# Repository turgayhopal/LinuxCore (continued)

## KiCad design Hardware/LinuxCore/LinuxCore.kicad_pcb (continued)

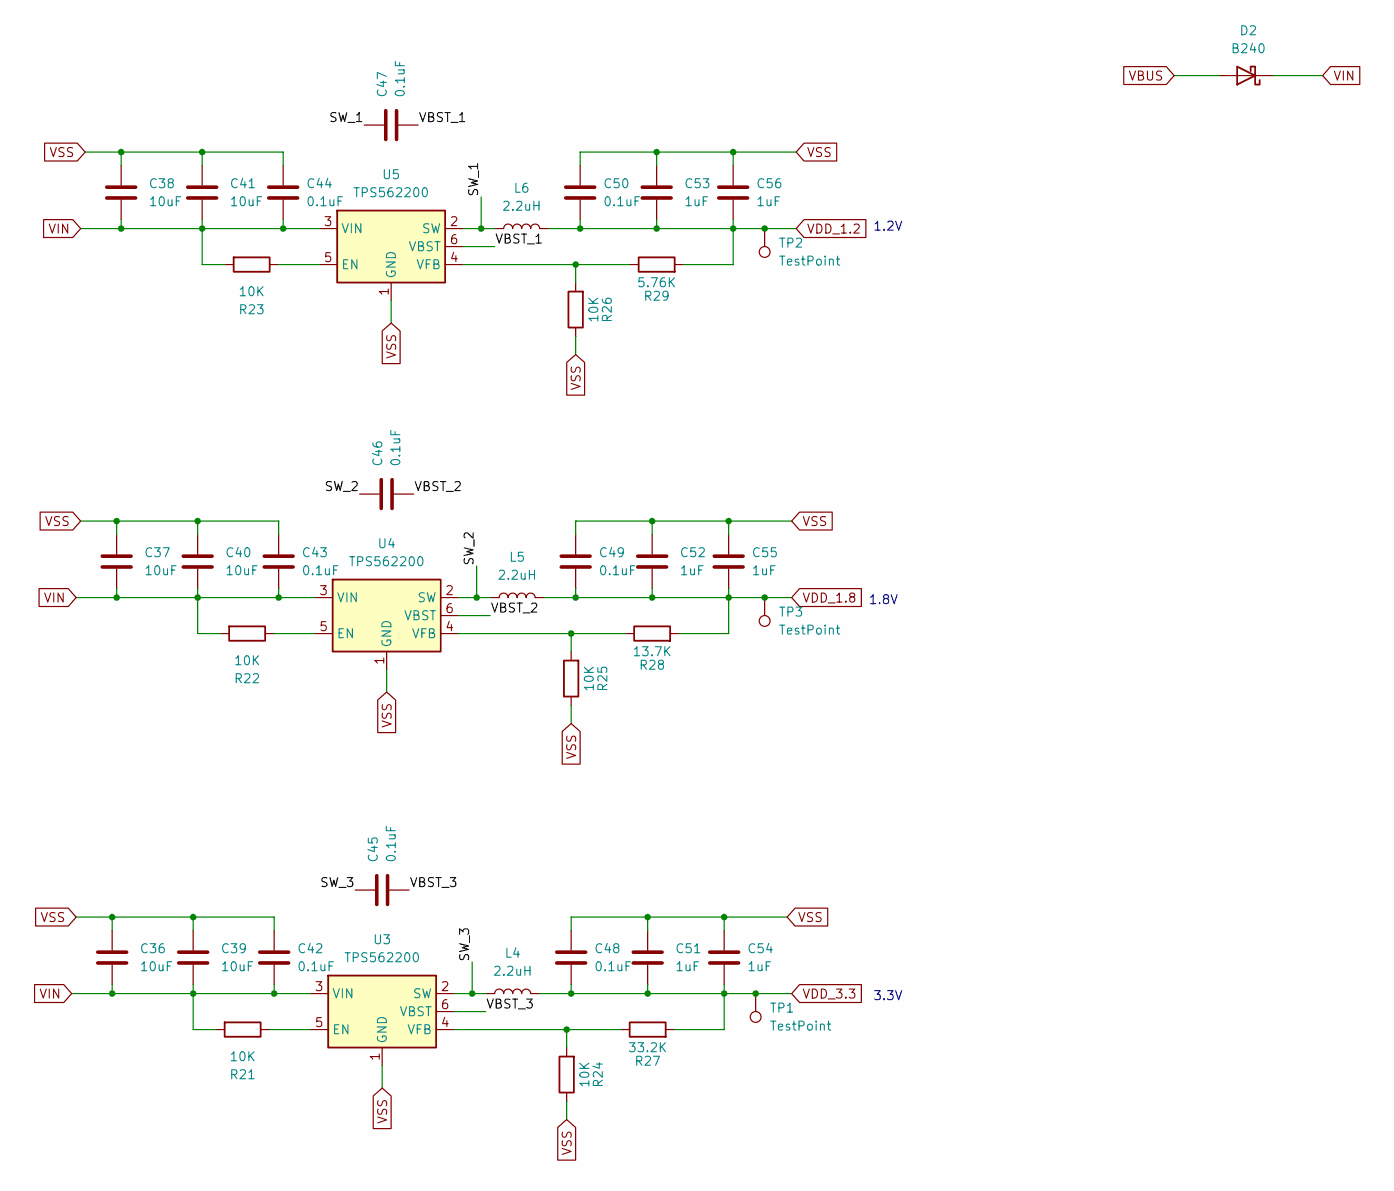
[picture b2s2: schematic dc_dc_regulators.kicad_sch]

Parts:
C36, C37, C38, C39, C40, C41: 10uF; C_0402_1005Metric
C42, C43, C44, C45, C46, C47, C48, C49, C50: 0.1uF; C_0402_1005Metric
C51, C52, C53, C54, C55, C56: 1uF; C_0402_1005Metric
D2: B240; D_SOD-123
L4, L5, L6: 2.2uH; L_Wuerth_MAPI-3020
R21, R22, R23, R24, R25, R26: 10K; R_0402_1005Metric
R27: 33.2K; R_0402_1005Metric
R28: 13.7K; R_0402_1005Metric
R29: 5.76K; R_0402_1005Metric
TP1, TP2, TP3: TestPoint; TestPoint_Pad_D1.0mm
U3, U4, U5: TPS562200; SOT-23-6

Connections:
/DC-DC Regulators/SW_1: C47.2, L6.1, U5.2 (SW)
/DC-DC Regulators/SW_2: C46.2, L5.1, U4.2 (SW)
/DC-DC Regulators/SW_3: C45.2, L4.1, U3.2 (SW)
/DC-DC Regulators/VBST_1: C47.1, U5.6 (VBST)
/DC-DC Regulators/VBST_2: C46.1, U4.6 (VBST)
/DC-DC Regulators/VBST_3: C45.1, U3.6 (VBST)
unnamed: R21.1, U3.5 (EN)
unnamed: R22.1, U4.5 (EN)
unnamed: R23.1, U5.5 (EN)
unnamed: R24.2, R27.1, U3.4 (VFB)
unnamed: R25.2, R28.1, U4.4 (VFB)
unnamed: R26.2, R29.1, U5.4 (VFB)
VBUS: D2.2 (A); also elsewhere on the board
VDD_1.2: C50.2, C53.2, C56.2, L6.2, R29.2, TP2.1; also elsewhere on the board
VDD_1.8: C49.2, C52.2, C55.2, L5.2, R28.2, TP3.1; also elsewhere on the board
VDD_3.3: C48.2, C51.2, C54.2, L4.2, R27.2, TP1.1; also elsewhere on the board
VIN: C36.2, C37.2, C38.2, C39.2, C40.2, C41.2, C42.2, C43.2, C44.2, D2.1 (K), R21.2, R22.2, R23.2, U3.3 (VIN), U4.3 (VIN), U5.3 (VIN)
VSS: C36.1, C37.1, C38.1, C39.1, C40.1, C41.1, C42.1, C43.1, C44.1, C48.1, C49.1, C50.1, C51.1, C52.1, C53.1, C54.1, C55.1, C56.1, R24.1, R25.1, R26.1, U3.1 (GND), U4.1 (GND), U5.1 (GND); also elsewhere on the board

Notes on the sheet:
1.2V
3.3V
1.8V

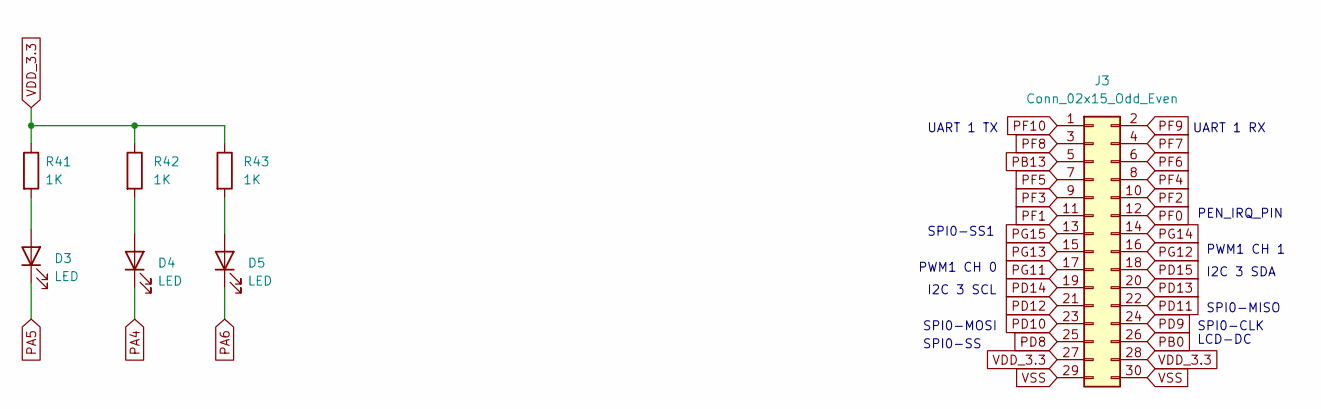
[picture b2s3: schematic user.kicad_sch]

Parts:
D3, D4, D5: LED; LED_0603_1608Metric
J3: Conn_02x15_Odd_Even; PinHeader_2x15_P2.54mm_Vertical
R41, R42, R43: 1K; R_0402_1005Metric

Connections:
unnamed: D3.2 (A), R41.2
unnamed: D4.2 (A), R42.2
unnamed: D5.2 (A), R43.2
PA4: D4.1 (K); also elsewhere on the board
PA5: D3.1 (K); also elsewhere on the board
PA6: D5.1 (K); also elsewhere on the board
PB0: J3.26; also elsewhere on the board
PB13: J3.5; also elsewhere on the board
PD8: J3.25; also elsewhere on the board
PD9: J3.24; also elsewhere on the board
PD10: J3.23; also elsewhere on the board
PD11: J3.22; also elsewhere on the board
PD12: J3.21; also elsewhere on the board
PD13: J3.20; also elsewhere on the board
PD14: J3.19; also elsewhere on the board
PD15: J3.18; also elsewhere on the board
PF0: J3.12; also elsewhere on the board
PF1: J3.11; also elsewhere on the board
PF2: J3.10; also elsewhere on the board
PF3: J3.9; also elsewhere on the board
PF4: J3.8; also elsewhere on the board
PF5: J3.7; also elsewhere on the board
PF6: J3.6; also elsewhere on the board
PF7: J3.4; also elsewhere on the board
PF8: J3.3; also elsewhere on the board
PF9: J3.2; also elsewhere on the board
PF10: J3.1; also elsewhere on the board
PG11: J3.17; also elsewhere on the board
PG12: J3.16; also elsewhere on the board
PG13: J3.15; also elsewhere on the board
PG14: J3.14; also elsewhere on the board
PG15: J3.13; also elsewhere on the board
VDD_3.3: J3.27, J3.28, R41.1, R42.1, R43.1; also elsewhere on the board
VSS: J3.29, J3.30; also elsewhere on the board

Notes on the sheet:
SPI0-MOSI
I2C 3 SCL
UART 1 TX
SPI0-SS
PWM1 CH 0
SPI0-SS1
PEN_IRQ_PIN
SPI0-CLK
PWM1 CH 1
UART 1 RX
SPI0-MISO
I2C 3 SDA
LCD-DC

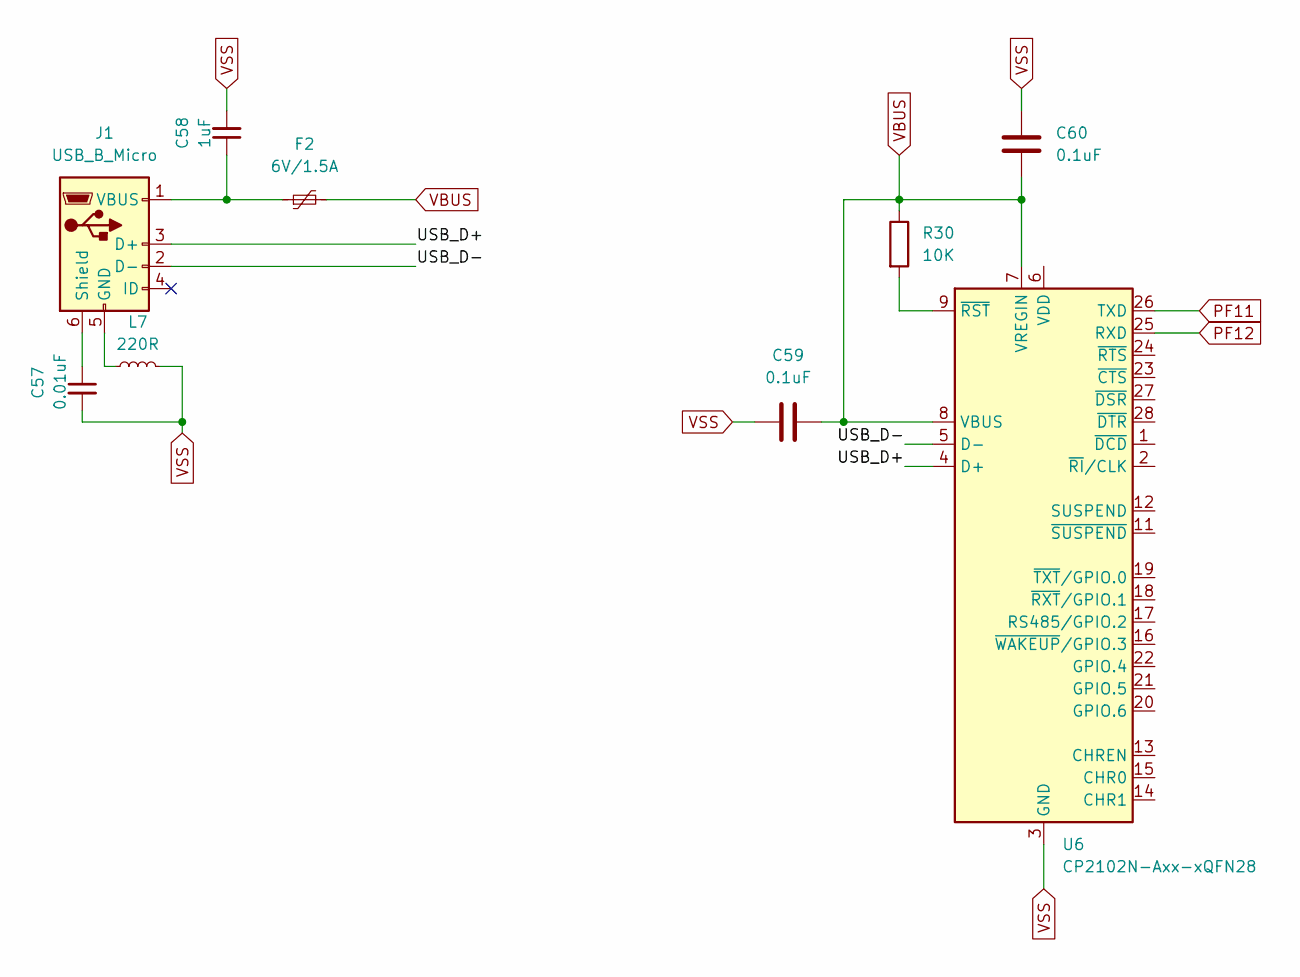
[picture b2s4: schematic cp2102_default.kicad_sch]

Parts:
C57: 0.01uF; C_0402_1005Metric
C58: 1uF; C_0402_1005Metric
C59, C60: 0.1uF; C_0402_1005Metric
F2: 6V/1.5A; Fuse_0805_2012Metric
J1: USB_B_Micro; USB_Micro-B_Amphenol_10118194_Horizontal
L7: 220R; L_0603_1608Metric
R30: 10K; R_0402_1005Metric
U6: CP2102N-Axx-xQFN28; QFN-28-1EP_5x5mm_P0.5mm_EP3.35x3.35mm

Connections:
/CP2102/USB_D+: J1.3 (D+), U6.4 (D+)
/CP2102/USB_D-: J1.2 (D-), U6.5 (D-)
unnamed: C57.1, J1.6 (Shield)
unnamed: C58.1, F2.1, J1.1 (VBUS)
unnamed: J1.5 (GND), L7.1
unnamed: R30.2, U6.9 (~RST)
PF11: U6.26 (TXD); also elsewhere on the board
PF12: U6.25 (RXD); also elsewhere on the board
VBUS: C59.2, C60.1, F2.2, R30.1, U6.7 (VREGIN), U6.8 (VBUS); also elsewhere on the board
VSS: C57.2, C58.2, C59.1, C60.2, L7.2, U6.3 (GND), U6.29 (GND); also elsewhere on the board

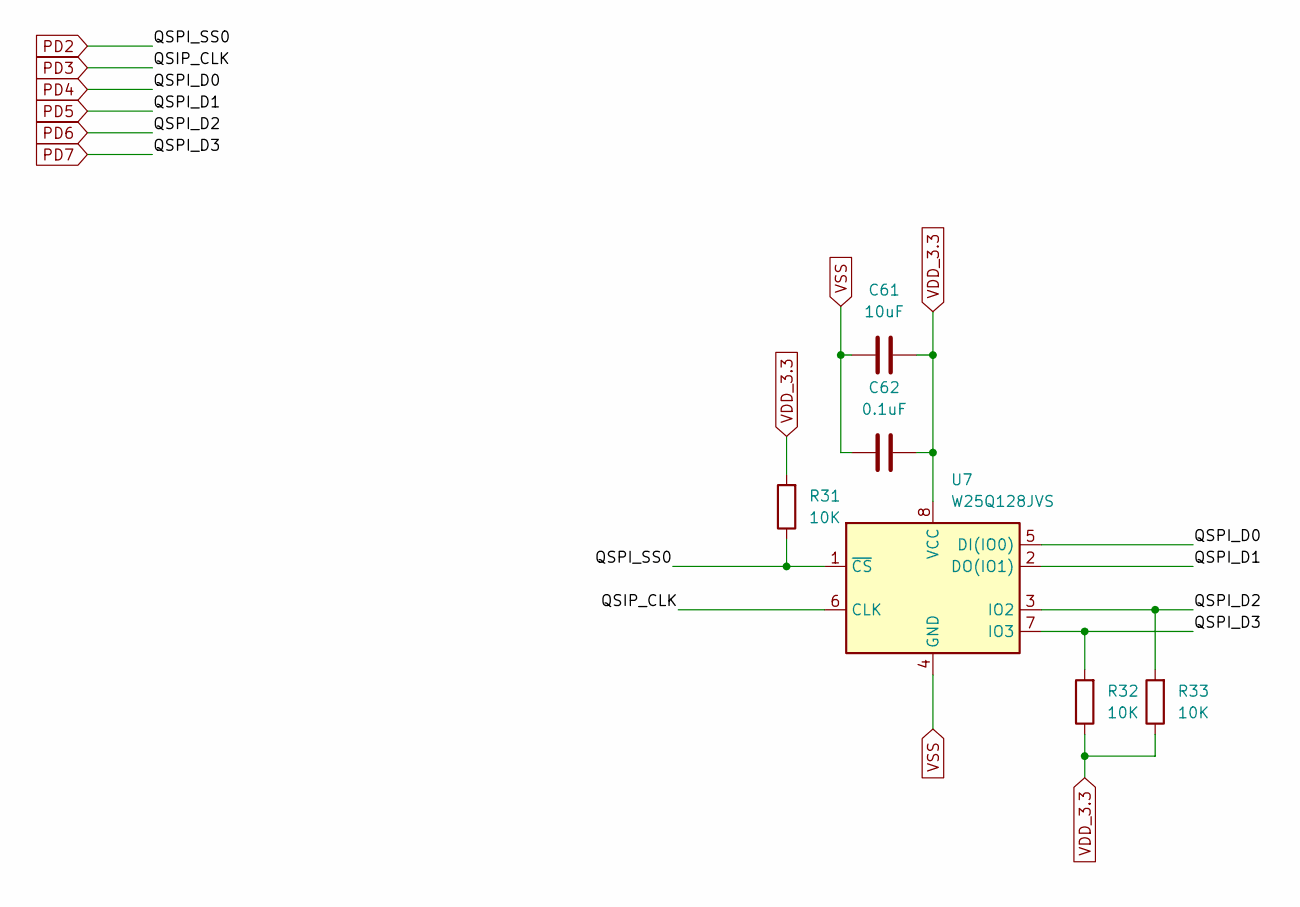
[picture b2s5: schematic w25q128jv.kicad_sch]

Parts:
C61: 10uF; C_0402_1005Metric
C62: 0.1uF; C_0402_1005Metric
R31, R32, R33: 10K; R_0402_1005Metric
U7: W25Q128JVS; SOIC-8_5.23x5.23mm_P1.27mm

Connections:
PD2: R31.1, U7.1 (~CS); also elsewhere on the board
PD3: U7.6 (CLK); also elsewhere on the board
PD4: U7.5 (DI(IO0)); also elsewhere on the board
PD5: U7.2 (DO(IO1)); also elsewhere on the board
PD6: R33.2, U7.3 (IO2); also elsewhere on the board
PD7: R32.2, U7.7 (IO3); also elsewhere on the board
VDD_3.3: C61.2, C62.2, R31.2, R32.1, R33.1, U7.8 (VCC); also elsewhere on the board
VSS: C61.1, C62.1, U7.4 (GND); also elsewhere on the board

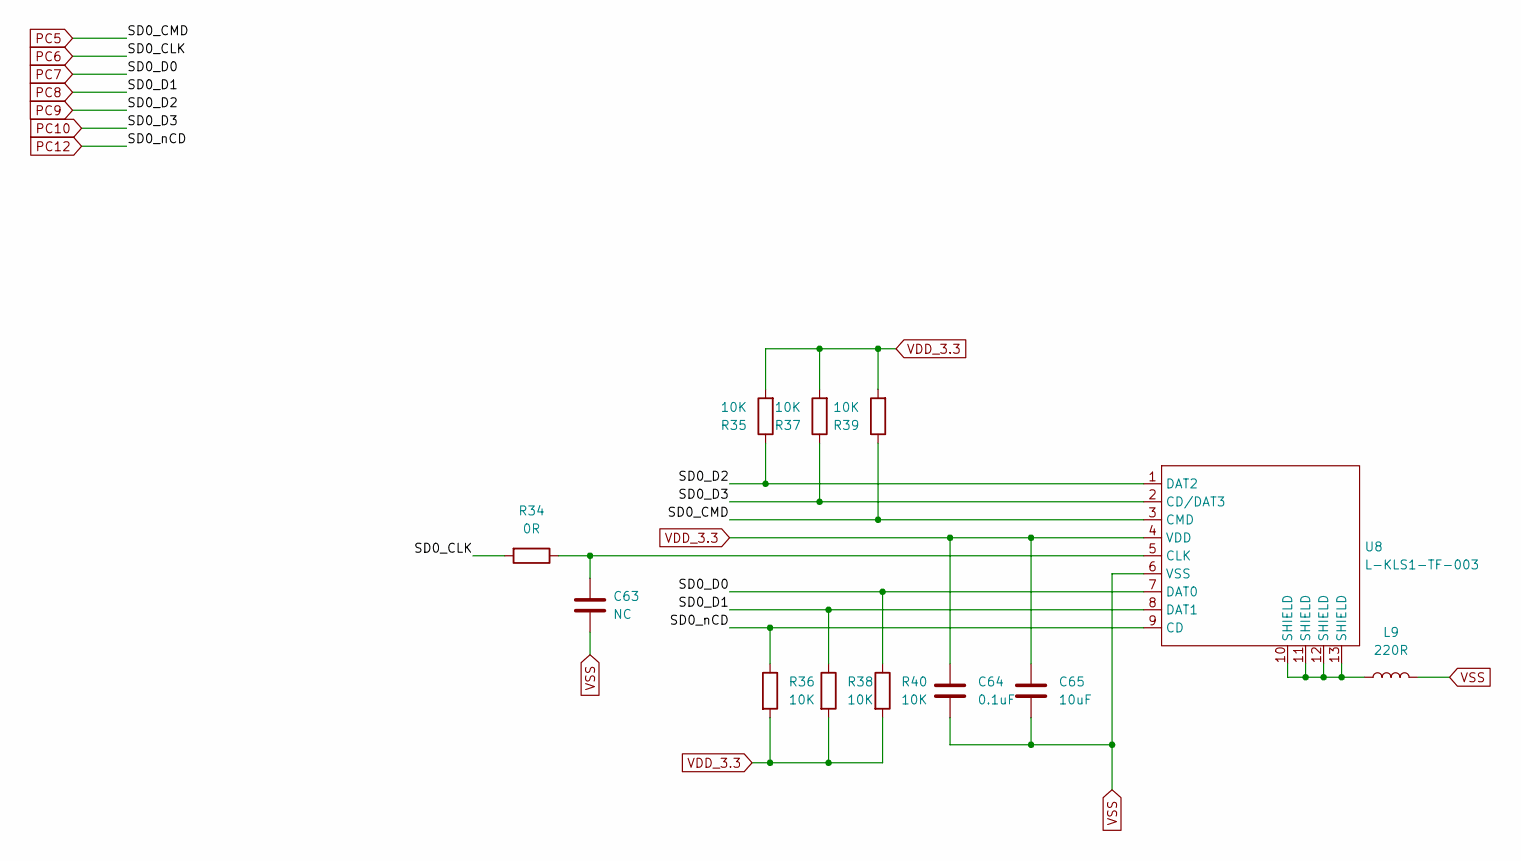
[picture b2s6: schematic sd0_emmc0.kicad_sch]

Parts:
C63: NC; C_0402_1005Metric
C64: 0.1uF; C_0402_1005Metric
C65: 10uF; C_0402_1005Metric
L9: 220R; L_0603_1608Metric
R34: 0R; R_0402_1005Metric
R35, R36, R37, R38, R39, R40: 10K; R_0402_1005Metric
U8: L-KLS1-TF-003; L-KLS1-TF-003-H1.85-R

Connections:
unnamed: C63.1, R34.1, U8.5 (CLK)
unnamed: L9.1, U8.10 (SHIELD), U8.11 (SHIELD), U8.12 (SHIELD), U8.13 (SHIELD)
PC5: R39.1, U8.3 (CMD); also elsewhere on the board
PC6: R34.2; also elsewhere on the board
PC7: R40.1, U8.7 (DAT0); also elsewhere on the board
PC8: R38.1, U8.8 (DAT1); also elsewhere on the board
PC9: R35.1, U8.1 (DAT2); also elsewhere on the board
PC10: R37.1, U8.2 (CD/DAT3); also elsewhere on the board
PC12: R36.1, U8.9 (CD); also elsewhere on the board
VDD_3.3: C64.1, C65.1, R35.2, R36.2, R37.2, R38.2, R39.2, R40.2, U8.4 (VDD); also elsewhere on the board
VSS: C63.2, C64.2, C65.2, L9.2, U8.6 (VSS); also elsewhere on the board

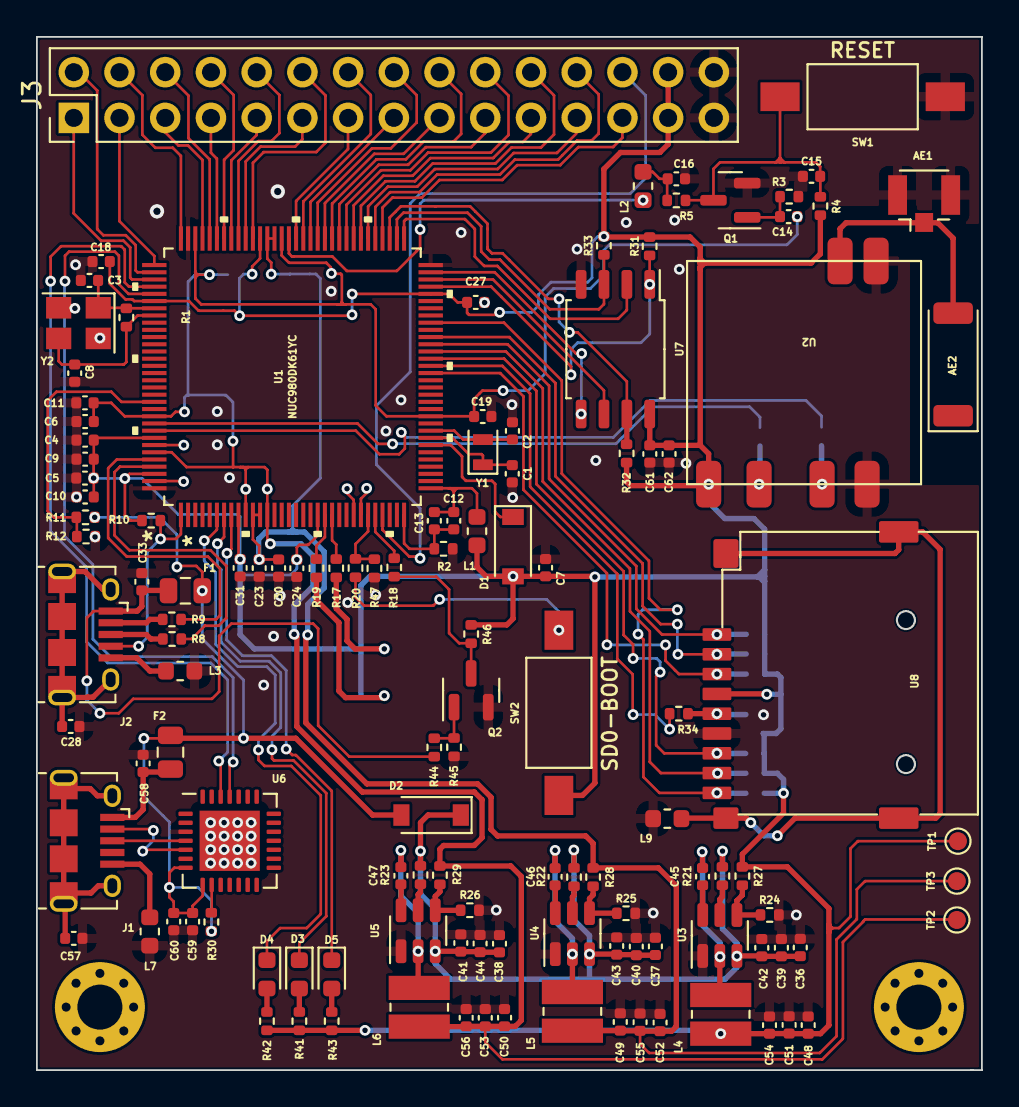
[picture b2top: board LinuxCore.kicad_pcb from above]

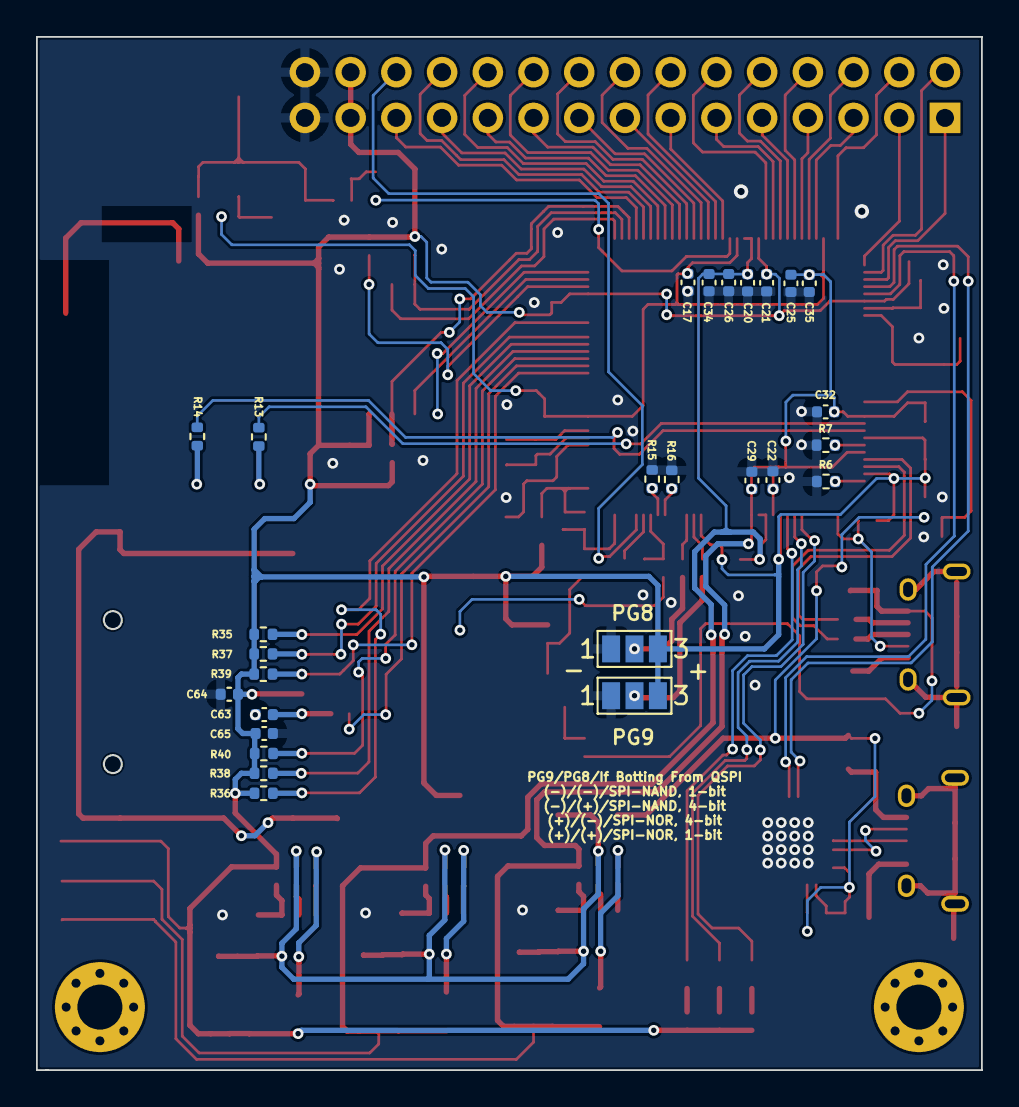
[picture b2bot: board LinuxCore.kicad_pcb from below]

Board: 2 copper layers, 52.5 x 57.4 mm, 151 parts (27 on the bottom side), 111 nets.

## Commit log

2022-09-05 Update Board
2024-09-30 update 3d model
